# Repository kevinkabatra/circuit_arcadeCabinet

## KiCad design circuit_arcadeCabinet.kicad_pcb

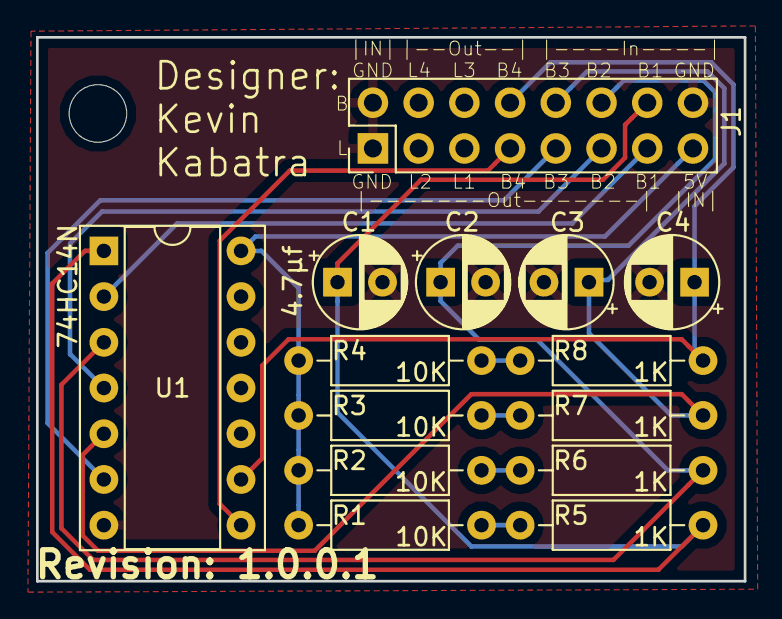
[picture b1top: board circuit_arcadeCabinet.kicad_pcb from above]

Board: 2 copper layers, 39.3 x 30.2 mm, 14 parts (0 on the bottom side), 14 nets.

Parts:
C1, C2, C3, C4: 4.7µf; CP_Radial_D5.0mm_P2.50mm
J1: Conn_02x08_Counter_Clockwise; PinHeader_2x08_P2.54mm_Vertical
R1, R2, R3, R4: 10K; R_Axial_DIN0207_L6.3mm_D2.5mm_P10.16mm_Horizontal
R5, R6, R7, R8: 1K; R_Axial_DIN0207_L6.3mm_D2.5mm_P10.16mm_Horizontal
U1: 74HC14N; DIP-14_W7.62mm_Socket

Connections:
5V: J1.15, R1.2, R2.2, R3.2, R4.2, U1.14
GND: C1.2, C2.2, C3.2, C4.2, J1.1, J1.2, J1.16, U1.7
Load_State_Input: C3.1, J1.10, R7.1, U1.5
Load_State_Ouput: J1.9, U1.6
unnamed: R1.1, R5.2
unnamed: R2.1, R6.2
unnamed: R3.1, R7.2
unnamed: R4.1, R8.2
Player_1_Coin_Input: C1.1, J1.14, R5.1, U1.1
Player_1_Coin_Output: J1.13, U1.2
Player_2_Coin_Input: C2.1, J1.12, R6.1, U1.3
Player_2_Coin_Output: J1.11, U1.4
Save_State_Input: C4.1, J1.8, R8.1, U1.9
Save_State_Output: J1.7, U1.8

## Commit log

2018-09-18 PCB v1.0.0.0
2018-09-30 version sent off to fabrication
2019-01-21 Massive update

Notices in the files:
circuit_arcadeCabinet.kicad_pcb:
Designed by Kevin Kabatra and released under MIT license.
